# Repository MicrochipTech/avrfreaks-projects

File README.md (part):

# AVRFreaks Projects

The projects listed here are not owned nor managed by Microchip Technology Incorporated. See [Website Terms and Conditions](https://www.microchip.com/en-us/about/legal-information/website-terms-and-conditions) for terms and conditions.

## Projects

- [FatFS SD Card atmega328p](projects/fatfs-sd-card-atmega328p)
- [simple CAN TRANSMITTER & CAN RECEIVER with ATTINY804 , MCP2515 in ASSEMBLY](projects/simple-can-transmitter-can-receiver-attiny804-mcp2515-assembly)
- [USB HID Volume Control using ATmega16 with Rotary Encoder input](projects/usb-hid-volume-control-using-atmega16-rotary-encoder-input)
- [MAX7219 LED MATRIX clock with DS3231 and ATTINY 804 in ASSEMBLY](projects/max7219-led-matrix-clock-ds3231-and-attiny-804-assembly)
- [prnf](projects/prnf)
- [How-to select an optimal AVR type](projects/how-select-optimal-avr-type)
- [FP_display_for_UNO_V2](projects/fpdisplayforunov2)
- [DS1307 clock with menu , Attiny804, Assembly](projects/ds1307-clock-menu-attiny804-assembly)
- [HX711 raw data reader,Attiny804,assembly](projects/hx711-raw-data-readerattiny804assembly)
- [HX-711 , Attiny804 weighing scale ,ASM , assembly](projects/hx-711-attiny804-weighing-scale-asm-assembly)
- [Mouse Mover](projects/mouse-mover)
- [Floating_point_numbers: An investigation](projects/floatingpointnumbers-investigation)
- [Interfacing SSD1306 based 128x64 I2C OLED module without Frame Buffer and 4 input keys with 8-pin ATtiny85 in Assembly Code](projects/interfacing-ssd1306-based-128x64-i2c-oled-module-without-frame-buffer-and-4-input-keys-8)
- [Floating point display for the UNO](projects/floating-point-display-uno)
- [temperature controlled dc fan using atmega8](projects/temperature-controlled-dc-fan-using-atmega8)
- [APL - VGA, Audio and PS2 keyboard library](projects/apl-vga-audio-and-ps2-keyboard-library)
- [WB2812_Tiny25](projects/wb2812tiny25)
- [UNO_as_UPDI_programmer](projects/unoasupdiprogrammer)
- [Attiny804 basic USART transmit in assembly](projects/attiny804-basic-usart-transmit-assembly)
- [8086 emulator on Arduino UNO (atmega328p)](projects/8086-emulator-arduino-uno-atmega328p)
- [Attiny10 OLED Simple I2C Bitbang master in assembly with fonts](projects/attiny10-oled-simple-i2c-bitbang-master-assembly-fonts)
- [Attiny13 200psi pressure gauge 1602 Hitachi LCD with I2C backpack bitbang](projects/attiny13-200psi-pressure-gauge-1602-hitachi-lcd-i2c-backpack-bitbang)
- [ATTINY 804 Simple hardware I2C for Hitachi1602 LCD](projects/attiny-804-simple-hardware-i2c-hitachi1602-lcd)
- [Keypad & LCD in AVR Assembler](projects/keypad-lcd-avr-assembler)
- [AVRjs](projects/avrjs)
- [LM35](projects/lm35)
- [SAMV71 XPlained Ultra -- QSPI MEMORY MODE -- DMA](projects/samv71-xplained-ultra-qspi-memory-mode-dma)
- [Labels Counter Rev2](projects/labels-counter-rev2)
- [AVRUtils - I/O Abstraction](projects/avrutils-io-abstraction)
- [A8Eprog 1.00](projects/a8eprog-100)
- [SD Card MIDI Player](projects/sd-card-midi-player)
- [Arduino RTC Alarm Clock](projects/arduino-rtc-alarm-clock)
- [Stepper motor drive for telescope](projects/stepper-motor-drive-telescope)
- [MEGA TETRIS board (ATmega RGB LED display with pack of classic games and UART control)](projects/mega-tetris-board-atmega-rgb-led-display-pack-classic-games-and-uart-control)
- [Universal I/O C++ classes that should work with all 8bit AVRs](projects/universal-io-c-classes-should-work-all-8bit-avrs)
- [Capacitance meter with a current source to measure C from 1 pF to 400+ mF range](projects/capacitance-meter-current-source-measure-c-1-pf-400-mf-range)
- [A 540 Lumen Bike Light](projects/540-lumen-bike-light)
- [Single Letter Reader](projects/single-letter-reader)
- [Another Led Game](projects/another-led-game)
- [Full duplex software serial port](projects/full-duplex-software-serial-port)
- [I2C EEPROM Library](projects/i2c-eeprom-library)
- [TCPSimDBG VB Example v1](projects/tcpsimdbg-vb-example-v1)
- [Butterfly_RTC_demo](projects/butterflyrtcdemo)
- [Two AVR USART Communication](projects/two-avr-usart-communication)
- [AVR Sim Debug , TCPSimDBG](projects/avr-sim-debug-tcpsimdbg)
- [YABC (yet another boring clock)](projects/yabc-yet-another-boring-clock)
- [Temperature alarm](projects/temperature-alarm)
- [ROBOCON 2009](projects/robocon-2009)
- [4x25W amplifier with usb control](projects/4x25w-amplifier-usb-control)
- [Simple Led Cross](projects/simple-led-cross)
- [hexapode](projects/hexapode)
- [tmep_collector](projects/tmepcollector)
- [8/16/32/64b Math routines v2.0](projects/8163264b-math-routines-v20)
- [Bin2Dec](projects/bin2dec)
- [LCF Meter v1.2](projects/lcf-meter-v12)
- [Hex to Ascii Blitzschnell](projects/hex-ascii-blitzschnell)
- [ATMEGA32 BOARD](projects/atmega32-board)
- [COMMUNICATION BETWEEN 2 MCU](projects/communication-between-2-mcu)
- [Mega644 video generation](projects/mega644-video-generation)
- [AVR sound Recorder with MMC](projects/avr-sound-recorder-mmc)
- [RPM & Temperature & Gass Monitor](projects/rpm-temperature-gass-monitor)
- [New explorer for Atmega](projects/new-explorer-atmega)
- [I2C external EEProm Library](projects/i2c-external-eeprom-library)
- [Driver display 320x240](projects/driver-display-320x240)
- [Connect SD/MMC to atmega](projects/connect-sdmmc-atmega)
- [A simple RPM ATmega8](projects/simple-rpm-atmega8)
- [Bluetooth Based Smart Home](projects/bluetooth-based-smart-home)
- [taskswitch](projects/taskswitch)
- [IR Remote Controlled Car](projects/ir-remote-controlled-car)
- [Temperature Data Logger](projects/temperature-data-logger)
- [Temperature meter](projects/temperature-meter)
- [attiny26 ADC convertion](projects/attiny26-adc-convertion)
- [attiny26 dual PWM output](projects/attiny26-dual-pwm-output)
- [NGW100 Led Blink C program AVR32](projects/ngw100-led-blink-c-program-avr32)
- [My development boards for ATmega](projects/my-development-boards-atmega)
- [Efficient key debounce](projects/efficient-key-debounce)
- [Fast/Easy Switch Debouncer](projects/fasteasy-switch-debouncer)
- [Fast raw AVR ethernet for I/O](projects/fast-raw-avr-ethernet-io)
- [Control DDS-60 RF Synthesizer](projects/control-dds-60-rf-synthesizer)
- [Sony IR Remote Decoder](projects/sony-ir-remote-decoder)
- [Morse Code Practice Unit](projects/morse-code-practice-unit)
- [TeslaPhonic Organ V2, (update)V3](projects/teslaphonic-organ-v2-updatev3)
- [simple 7-seg counter](projects/simple-7-seg-counter)
- [AVR BootLoader 4 Mega32](projects/avr-bootloader-4-mega32)
- [Digital comb filter (humnuller)](projects/digital-comb-filter-humnuller)
- [Temperature via AVR-USB](projects/temperature-avr-usb)
- [TLC4541 dirver - 16 bit AD by TI](projects/tlc4541-dirver-16-bit-ad-ti)
- [Timer0 Interrupt handling](projects/timer0-interrupt-handling)
- [ATMEGA8 Development Board](projects/atmega8-development-board)
- [Flexible 4 bit LCD mode](projects/flexible-4-bit-lcd-mode)
- [WINDOWS STUDIO+ IDE Source Code](projects/windows-studio-ide-source-code)
- [Remote Controlled Car](projects/remote-controlled-car)
- [M-sequence (MLS) Generator](projects/m-sequence-mls-generator)
- [Graphical LCD Oscilloscope V2.0](projects/graphical-lcd-oscilloscope-v20)
- [I2C EEPROM Reader/Writer](projects/i2c-eeprom-readerwriter)
- [Washing machine](projects/washing-machine)
- [Automatic pet feeder](projects/automatic-pet-feeder)
- [RC5 Receiver for 16 leds](projects/rc5-receiver-16-leds)
- [Digital capacimeter](projects/digital-capacimeter)
- [HF generator](projects/hf-generator)
- [Motorized astronomy telescope](projects/motorized-astronomy-telescope)
- [AP7 PS2 Keyboard Driver](projects/ap7-ps2-keyboard-driver)
- [Versatile digital speedometer](projects/versatile-digital-speedometer)
- [DS1821 Thermometer](projects/ds1821-thermometer)
- [Harddisk Interface](projects/harddisk-interface)
- [Reaction game with AVR 90s2313](projects/reaction-game-avr-90s2313)
- [4x4 Matrix Key-board Interfacing](projects/4x4-matrix-key-board-interfacing)
- [AP7 mouse driver](projects/ap7-mouse-driver)
- [Atmega2560 BootLoader](projects/atmega2560-bootloader)
- [Basic LED Prjct Using Interrupt](projects/basic-led-prjct-using-interrupt)
- [DIY ATmega32 Starter's Kit](projects/diy-atmega32-starters-kit)
- [CAN Bus Driver for AT90CAN128 including FreeRTOS interface](projects/can-bus-driver-at90can128-including-freertos-interface)
- [True Random Number Generator](projects/true-random-number-generator)
- [PWM DC motor control with mega8](projects/pwm-dc-motor-control-mega8)
- [8-Channel ADC with Atmega32](projects/8-channel-adc-atmega32)
- [NOKIA3310 LCD Thermometer](projects/nokia3310-lcd-thermometer)
- [AVCX: AVR based LCD controller](projects/avcx-avr-based-lcd-controller)
- [AVR Scope Clock shield V3.A](projects/avr-scope-clock-shield-v3a)
- [gps demo for EVK1100](projects/gps-demo-evk1100)
- [WiSHABI](projects/wishabi)
- [TI-99/4A PS/2 Keyboard Interface](projects/ti-994a-ps2-keyboard-interface)
- [AVR - Lego Car](projects/avr-lego-car)
- [Interfacing External Interrupts](projects/interfacing-external-interrupts)
- [EA DOG-M 16X SPI C++ Library](projects/ea-dog-m-16x-spi-c-library)
- [Analog measurements and logger](projects/analog-measurements-and-logger)
- [AVGA v0.2](projects/avga-v02)
- [PT-100 Temperature sensor](projects/pt-100-temperature-sensor)
- [Accelerometer Reader](projects/accelerometer-reader)
- [termostat](projects/termostat)
- [Brake light blink](projects/brake-light-blink)
- [Driver for Nand flash memory](projects/driver-nand-flash-memory)
- [Driver for display Nokia 6100](projects/driver-display-nokia-6100)
- [Homebrew Case for the STK-500](projects/homebrew-case-stk-500)
- [MultiKit Digital Oscilloscope](projects/multikit-digital-oscilloscope)
- [Lndkavr](projects/lndkavr)
- [DigitalFrame MiniCommander](projects/digitalframe-minicommander)
- [USB Dance Pad](projects/usb-dance-pad)
- [basic tune player](projects/basic-tune-player)
- [PWM mit ATMEGA8](projects/pwm-mit-atmega8)
- [Investment Banker Eliminator](projects/investment-banker-eliminator)
- [Function Gen on Scope Clock](projects/function-gen-scope-clock-0)
- [AVR/FPGA digital synthesizer](projects/avrfpga-digital-synthesizer)
- [AtMega8535 PF Correction Relay](projects/atmega8535-pf-correction-relay)
- [4-digit lock code](projects/4-digit-lock-code)
- [MIDI controller](projects/midi-controller)
- [PPPD PCB (STK200/300 programmer)](projects/pppd-pcb-stk200300-programmer)
- [zero cost Logic Analyzer](projects/zero-cost-logic-analyzer)
- [temprature control using at90853](projects/temprature-control-using-at90853)
- [LM34DZ Temp Sensor on AVR](projects/lm34dz-temp-sensor-avr)
- [Dallas one-wire interface](projects/dallas-one-wire-interface)
- [Driver for Hd44780 8bit data bus](projects/driver-hd44780-8bit-data-bus)
- [16x2 LCD Libraries.](projects/16x2-lcd-libraries)
- [ATmega8 Devlopment  Board](projects/atmega8-devlopment-board)
- [Interfacing 4 buttons to the AVR](projects/interfacing-4-buttons-avr)
- [First C Project](projects/first-c-project)
- [Metronome](projects/metronome-0)
- [AVR-mUPI: A Unified Programming Interface for ATMEL® megaAVR devices.](projects/avr-mupi-unified-programming-interface-atmel%C2%AE-megaavr-devices)
- [Modbus RTU Slave Library for the avr](projects/modbus-rtu-slave-library-avr)
- [TOSHIBA T6963C DISPLAY DRIVE MADE IN C++ FOR AVR](projects/toshiba-t6963c-display-drive-made-c-avr)
- [Eclipse plugin for UART communication using USBasp+ programmer](projects/eclipse-plugin-uart-communication-using-usbasp-programmer)
- [Soft timers](projects/soft-timers-0)
- [3 servo claw arm](projects/3-servo-claw-arm)
- [PhoenixU1 (porting the Unix v1 to Atmega 8-bit)](projects/phoenixu1-porting-unix-v1-atmega-8-bit)
- [simple programablle count down timer](projects/simple-programablle-count-down-timer)
- [HD44780 Display Drive V2.00 C++](projects/hd44780-display-drive-v200-c)
- [Loader and recorder for ZX Spectrum on SD/SDHC](projects/loader-and-recorder-zx-spectrum-sdsdhc)
- [PWM mixed  Drive using ATMega8](projects/pwm-mixed-drive-using-atmega8)
- [HWA : high-level, no penalty hardware abstraction for microcontrollers](projects/hwa-high-level-no-penalty-hardware-abstraction-microcontrollers)
- [AVR32 UC3 Assembly example](projects/avr32-uc3-assembly-example)
- [A PC to uC IR Messaging system](projects/pc-uc-ir-messaging-system)
- [Bangla Voice Calling Bell](projects/bangla-voice-calling-bell)
- [AVR SPI IO Expander](projects/avr-spi-io-expander)
- [Basic AVR IO for LED Bar](projects/basic-avr-io-led-bar)
- [AVR231 AES Boot Loader](projects/avr231-aes-boot-loader)
- [AVR313 - PS2 Keyboard](projects/avr313-ps2-keyboard)
- [16.16 signed binary math lib.](projects/1616-signed-binary-math-lib)
- [ATMEGA16 to NOKIA8310LCD](projects/atmega16-nokia8310lcd)
- [Household power logger](projects/household-power-logger)
- [ADC using capacitor](projects/adc-using-capacitor)
- [Up/Down Timer Clock](projects/updown-timer-clock)
- [OSCCAL Calibration Program](projects/osccal-calibration-program)
- [Robotic Rescue Vehicle](projects/robotic-rescue-vehicle)
- [Simple ADC interface with LDR](projects/simple-adc-interface-ldr)
- [Sharp's GP2D02 Digital IR sensor](projects/sharps-gp2d02-digital-ir-sensor)
- [AVR Color LCD 320x240](projects/avr-color-lcd-320x240)
- [STK500 Binary Counter Demo](projects/stk500-binary-counter-demo)
- [Simple Projects](projects/simple-projects)
- [Temperature by SMT160 & AVR](projects/temperature-smt160-avr)
- [AVR BASED _ pre-amplifier + AGC](projects/avr-based-pre-amplifier-agc)
- [MyUSB Vendor defined demo](projects/myusb-vendor-defined-demo)
- [Multitherm](projects/multitherm)
- [ATtiny24/44/84 STK500 Adapter](projects/attiny244484-stk500-adapter)
- [GAS Detector](projects/gas-detector)
- [LCD2USB Button Fixed for Windows](projects/lcd2usb-button-fixed-windows)
- [ADC Using ATmega32](projects/adc-using-atmega32)
- [hd61830 library](projects/hd61830-library)
- [AVR SuperMario](projects/avr-supermario)
- [Microcontroller Oscilloscope](projects/microcontroller-oscilloscope)
- [rgb leds controlled by I2C](projects/rgb-leds-controlled-i2c)
- [5x7 led matrix demo (beginners)](projects/5x7-led-matrix-demo-beginners)
- [Lcd Clock](projects/lcd-clock)
- [IR (InfraRed) AVR Downloader](projects/ir-infrared-avr-downloader)
- [Pulse shifter (lag and lead)](projects/pulse-shifter-lag-and-lead)
- [RC1 transmitter using AVR 8535](projects/rc1-transmitter-using-avr-8535)
- [UART with FIFO](projects/uart-fifo)
- [3 axis bipolar stepper motor..](projects/3-axis-bipolar-stepper-motor)
- [Control de Motor Paso a Paso](projects/control-de-motor-paso-paso)
- [I2C (TWI) Sniffer](projects/i2c-twi-sniffer)
- [ultrasonics water height level](projects/ultrasonics-water-height-level)
- [Chameleon](projects/chameleon)
- [avr 20 servo controller](projects/avr-20-servo-controller)
- [Wiz810MJ with Bascom-AVR](projects/wiz810mj-bascom-avr)
- [Delay LOOPs](projects/delay-loops)
- [Project Buggy](projects/project-buggy)
- [22-bit voltmeter using AD7714](projects/22-bit-voltmeter-using-ad7714)
- [Anchor Winch Controller](projects/anchor-winch-controller)
- [Learn Code Vision](projects/learn-code-vision)
- [ethernet enc28j60 mega32](projects/ethernet-enc28j60-mega32)
- [Telephone Keypad](projects/telephone-keypad)
- [SD card reader for ATMega48](projects/sd-card-reader-atmega48)
- [RC Signal Reader](projects/rc-signal-reader)
- [External EEPROMs](projects/external-eeproms)
- [V/F & SVP demo on ATAVRMC200](projects/vf-svp-demo-atavrmc200)
- [Push Button Interfacing(Newbies)](projects/push-button-interfacingnewbies)
- [Arduino POV](projects/arduino-pov)
- [Decorative LEDs (For newbies)](projects/decorative-leds-newbies)
- [pC/OS - RTOS (realtime-kernel)](projects/pcos-rtos-realtime-kernel)
- [SIRC Decoding - Sony 12-bit IR](projects/sirc-decoding-sony-12-bit-ir)
- [Serial Connection With Labview](projects/serial-connection-labview)
- [Serial_LCD](projects/seriallcd)
- [BC100](projects/bc100)
- [UART C++ library](projects/uart-c-library)
- [VGA Display for STK500/501](projects/vga-display-stk500501)
- [LED Matrix](projects/led-matrix)
- [AVR uisp adapter for breadboard](projects/avr-uisp-adapter-breadboard)
- [MCUMenuObj 0.2](projects/mcumenuobj-02)
- [LCD-Driver](projects/lcd-driver)
- [JDTC](projects/jdtc)
- [HD44780's STDIO bind](projects/hd44780s-stdio-bind)
- [PCD 8544 LCD Driver](projects/pcd-8544-lcd-driver)
- [Thermometer with SMT160 on 7-seg](projects/thermometer-smt160-7-seg)
- [SW-UART up to 460800 Baud](projects/sw-uart-460800-baud)
- [Ultrasonic Resonant Tracking](projects/ultrasonic-resonant-tracking)
- [Accumulated PWM sinewave](projects/accumulated-pwm-sinewave)
- [Simple Traffic light controller](projects/simple-traffic-light-controller-0)
- [InfraRed Receiver](projects/infrared-receiver)
- [ads7816p driver](projects/ads7816p-driver)
- [Program HCS412 and HCS515 memory](projects/program-hcs412-and-hcs515-memory)
- [ADC voltage on 7seg at ATMEGA8](projects/adc-voltage-7seg-atmega8)
- [Rijndael / AES](projects/rijndael-aes)
- [Run AVR's from < 1 Volt](projects/run-avrs-1-volt)
- [Atmega training board](projects/atmega-training-board)
- [2.4 GHz Wireless Development Kit](projects/24-ghz-wireless-development-kit)
- [Wireless accelerometer mouse](projects/wireless-accelerometer-mouse)
- [Sound measuring decibel meter](projects/sound-measuring-decibel-meter)
- [my_ds18b20](projects/myds18b20)
- [ATtiny12 Stepper Motor Driver](projects/attiny12-stepper-motor-driver)
- [New Idea](projects/new-idea)
- [LotusLaser](projects/lotuslaser)
- [AVR 2.4 GHz  wireless RF module](projects/avr-24-ghz-wireless-rf-module)
- [XRay Dosimeter](projects/xray-dosimeter)
- [2D and 3D video on mega32](projects/2d-and-3d-video-mega32)
- [Conway's AI-Life for an AVR](projects/conways-ai-life-avr)
- [Dehumidifier Pump](projects/dehumidifier-pump)
- [WinLCDBitMap Version 1.0](projects/winlcdbitmap-version-10)
- [Pressure and stroke sensor](projects/pressure-and-stroke-sensor)
- [Isolated DC/DC Converter](projects/isolated-dcdc-converter)
- [Disassembler ATMEL AVR](projects/disassembler-atmel-avr)
- [Open GPS Tracker](projects/open-gps-tracker)
- [project](projects/project)
- [Network Biometric Authentication](projects/network-biometric-authentication)
- [AVR32 UC3 Serial Data Analyzer](projects/avr32-uc3-serial-data-analyzer)
- [Throttle System](projects/throttle-system)
- [LCD HD44780 C++ library](projects/lcd-hd44780-c-library)
- [Exposure timer](projects/exposure-timer)
- [Vacuum Tube Tester](projects/vacuum-tube-tester)
- [A (very) general controller](projects/very-general-controller)
- [Big Capacitor Stepper](projects/big-capacitor-stepper)
- [Programmable Relay](projects/programmable-relay)
- [Student Mega32 projects 2008](projects/student-mega32-projects-2008)
- [4x4x1](projects/4x4x1)
- [AVRsulabh- Parallel Programmer](projects/avrsulabh-parallel-programmer)
- [Nikon IR release](projects/nikon-ir-release)
- [Interrupt-based USART output](projects/interrupt-based-usart-output)
- [interrupt controlled button](projects/interrupt-controlled-button)
- [WebCam servo control](projects/webcam-servo-control)
- [Onewire lock system](projects/onewire-lock-system)
- [UAV parafoil](projects/uav-parafoil)
- [UTFT Fork which supports Fonts created by The Dot Factory](projects/utft-fork-which-supports-fonts-created-dot-factory)
- [hello_arduino](projects/helloarduino)
- [Motion Detector,Video Generator,Video GenLock with atmega64,atmega128](projects/motion-detectorvideo-generatorvideo-genlock-atmega64atmega128)
- [AVR Assembler Library for all microcontrollers with SRAM](projects/avr-assembler-library-all-microcontrollers-sram)
- [FeedTimer with ATMega328P](projects/feedtimer-atmega328p)
- [WS2812 LED Drive for ATmega8, ATMEGA162, ATmega128, ATmega328P](projects/ws2812-led-drive-atmega8-atmega162-atmega128-atmega328p)
- [Fix garage door with ATmega328p](projects/fix-garage-door-atmega328p)
- [Scientific Calculator](projects/scientific-calculator)
- [cojson - a JSON parser/generator for constrained platforms](projects/cojson-json-parsergenerator-constrained-platforms)
- [Tardyon Drive AVR Stepper Controller](projects/tardyon-drive-avr-stepper-controller)
- [FT232RL with optocouplers](projects/ft232rl-optocouplers)
- [A hotplug-capable DS1621/DS1631 temperature sensor library for the AVR](projects/hotplug-capable-ds1621ds1631-temperature-sensor-library-avr)
- [MAMoRo - Robot Platform](projects/mamoro-robot-platform)
- [sos Fuses manipulator for ATmega](projects/sos-fuses-manipulator-atmega)
- [FATEX-SD for EVK1100](projects/fatex-sd-evk1100)
- [AVRCryptoLib](projects/avrcryptolib)
- [M32 Clock Project](projects/m32-clock-project)
- [Control library for AD9833  DDS](projects/control-library-ad9833-dds)
- [Fuse Wizard](projects/fuse-wizard)
- [2 axis acceleration sensor](projects/2-axis-acceleration-sensor)
- [music recognizing dancing puppet](projects/music-recognizing-dancing-puppet)
- [Magic Laser aperture](projects/magic-laser-aperture)
- [uIP-0.9 With ENC18J60 Driver](projects/uip-09-enc18j60-driver)
- [MOS6581 SID Synthesizer](projects/mos6581-sid-synthesizer)
- [Power regulator/timer(ATMega8)](projects/power-regulatortimeratmega8)
- [Simple reaction tester with LCD](projects/simple-reaction-tester-lcd)
- [Countdown timer (ATtiny2313)](projects/countdown-timer-attiny2313)
- [uOLED-128-GMD1 interface](projects/uoled-128-gmd1-interface)
- [PID controller with anti-windup](projects/pid-controller-anti-windup)
- [Elmcie L- and C-meter](projects/elmcie-l-and-c-meter)
- [Moving average filter](projects/moving-average-filter)
- [ATtiny26 USI UART](projects/attiny26-usi-uart)
- [Servo driven robotic gripper](projects/servo-driven-robotic-gripper)
- [The Game of Life on an AVR](projects/game-life-avr)
- [LCD over one wire with ATtiny25](projects/lcd-over-one-wire-attiny25)
- [1-wire monitor](projects/1-wire-monitor)
- [Okapi](projects/okapi)
- [Resistor Network Calculator](projects/resistor-network-calculator)
- [Uni-polar stepper motor](projects/uni-polar-stepper-motor)
- [stepper motor driver](projects/stepper-motor-driver-1)
- [MMC Unlocker](projects/mmc-unlocker)
- [AVR DDS signal generator V2.0](projects/avr-dds-signal-generator-v20)
- [MidiController](projects/midicontroller)
- [Simple Traffic Light Controller](projects/simple-traffic-light-controller)
- [Cover paper for AVR Dragon kit](projects/cover-paper-avr-dragon-kit)
- [AVR Oscilloscope Clock](projects/avr-oscilloscope-clock)
- [AVR Flash Loader](projects/avr-flash-loader)
- [Terminalator II - The SQL](projects/terminalator-ii-sql)
- [AVR DB101 Demo gcc-Port](projects/avr-db101-demo-gcc-port)
- [trf24g RF module code](projects/trf24g-rf-module-code)
- [nRF2401 radio library](projects/nrf2401-radio-library)
- [library for 24cxx and 93cxx](projects/library-24cxx-and-93cxx)
- [Simple M168 Based Logic Analyzer](projects/simple-m168-based-logic-analyzer)
- [Fast LCD driver library](projects/fast-lcd-driver-library)
- [RF-talk](projects/rf-talk)
- [STK500 Example 2](projects/stk500-example-2)
- [9 floor elevator asm program](projects/9-floor-elevator-asm-program)
- [Speed Autobaud](projects/speed-autobaud)
- [CRC32 calculation functions](projects/crc32-calculation-functions)
- [Lib For Buffer](projects/lib-buffer)
- [AVR Oscilloscope Terminal](projects/avr-oscilloscope-terminal)
- [AVR446 ported for gcc](projects/avr446-ported-gcc)
- [Developer Terminal in C# and VB](projects/developer-terminal-c-and-vb)
- [YAVRTOS](projects/yavrtos)
- [Sparcle](projects/sparcle)
- [Intel Hex File Display Utility](projects/intel-hex-file-display-utility)
- [Refrash routine displays 240x320](projects/refrash-routine-displays-240x320)
- [YALBlinkie](projects/yalblinkie)
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
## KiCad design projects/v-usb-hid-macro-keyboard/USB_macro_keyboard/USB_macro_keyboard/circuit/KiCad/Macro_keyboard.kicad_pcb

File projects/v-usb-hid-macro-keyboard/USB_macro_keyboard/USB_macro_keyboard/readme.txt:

This is a package for project USB Macro_keyboard.

Main purpose of this project is to automate keboard presses with external tool that doesn't 
require install aditional software (so it works even on login screen of Windows OS or in BIOS).
It uses default HID keyboard drivers.

Sequence of keyboard signals is stored in eeprom. It can be uploaded via commandline tool or 
via standard SPI programming interface (although it might not be easy to get a proper addressing 
and also the attached schematic doesn't implement any programming connector on SPI interface).

Before programing make sure that your OS keyboard setting does match key mapping at the end of hid.c file.
To alter the code for your keyboard layout you can use table in Appendix C of Keyboard_scancodes_specification.pdf.
Additionals codes are in hid_keys.h that are also stored in eeprom memory but are used for device control
(e.g. timer delay - See function parseKeyBuffer in main.c file).

Original goal was to also create Windows program that can upload data to this device.
Unfortunately Windows handle keyboard drivers in a specific way and doesn't allow access to the device.
Because of that I decided to use signal on Num- and Caps-lock LEDs which are part of most of the keyboards.
After several presses of Num- and Caps-lock (or their combinations) it triggers corresponding procedure.

The commandline tool included is operating without too much problem on Linux system.
User has to have an access to USB ports or have root privilege. Also libusb-1.0 library is required.

Other limitation of this device is that it can only send key press and imidiate release. It can't
hold the key pressed for longer duration. Also it can send only one key at the time (not counting
modifiers keys like ctrl, alt and shift).

Special options can be selected in main_config.h (for example remove print function and some of the keys
to fit the code in attiny45) and usbconfig.h (change vendor/device name and VID/PID).

===Note for tiny85 clock source======================

Attiny85 can use its internal oscillator (with some calibration) to generate 16.5 MHz clock source.
I personaly can't recommend it since it was not reliable in my case. Sometimes the calibration
was not done correctly and the device didn't properly connect to USB driver. Therefore I decided
to use 12 MHz crystal instead.

At first I used whole calibration range but it never connected. USB specification probably require
faster device connection.
On second try I used only very small part of it but that required first to find out close to optimal
value of OSCCAL register. This was quite different between 2 chips I tested so the build phase
of the device was not simple.

Some of that old code is located in misc folder if you want to try it.

===Thanks goes to====================================

Objective development for V-USB library   https://www.obdev.at/products/vusb/index.html
Frank Zhao for explanation of HID descriptors   http://eleccelerator.com/tutorial-about-usb-hid-report-descriptors/
Joonas Pihlajamaa and his password generator example   http://codeandlife.com/2012/03/03/diy-usb-password-generator/

===Licensing========================================

Files in usbdrv folders are part of V-USB library from OBJECTIVE DEVELOPMENT Software GmbH - see License.txt
in that folder.

Other files are released under GNU GPLv3 license. See license.txt in root folder of this project.

===Content of the package===========================

circuit
	KiCad
		CustomPCD.pretty
			Diode_Zener.kicad_mod
			SOIC-8S2.kicad_mod
			USB_A_male.kicad_mod
		fp-lib-table
		Macro_keyboard-cache.lib
		Macro_keyboard.kicad_pcb
		Macro_keyboard.net
		Macro_keyboard.pro
		Macro_keyboard.sch
	PCB_bottom_mirrored.pdf
	Schematic.pdf
commandline
	macro_keyboard.cpp
	Makefile
firmware
	hid.c
	hid.h
	hid_keys.h
	hid_rq.h
	main.c
	main_config.h
	main.h
	Makefile
	timer.h
	usbconfig.h
	usbdrv
		asmcommon.inc
		CommercialLicense.txt
		Changelog.txt
		License.txt
		oddebug.c
		oddebug.h
		Readme.txt
		usbconfig-prototype.h
		usbdrvasm.asm
		usbdrvasm.lst
		usbdrvasm.o
		usbdrvasm.S
		usbdrvasm12.inc
		usbdrvasm128.inc
		usbdrvasm15.inc
		usbdrvasm16.inc
		usbdrvasm165.inc
		usbdrvasm18-crc.inc
		usbdrvasm20.inc
		usbdrv.c
		usbdrv.h
		USB-ID-FAQ.txt
		USB-IDs-for-free.txt
		usbportability.h
license.txt
misc
	bottom.jpg
	HID1_11.pdf
	Keyboard_scancodes_specification.pdf
	Old_code
		hid.c
		usbconfig.h
	side.jpg
	top.jpg
readme.txt

===================================================

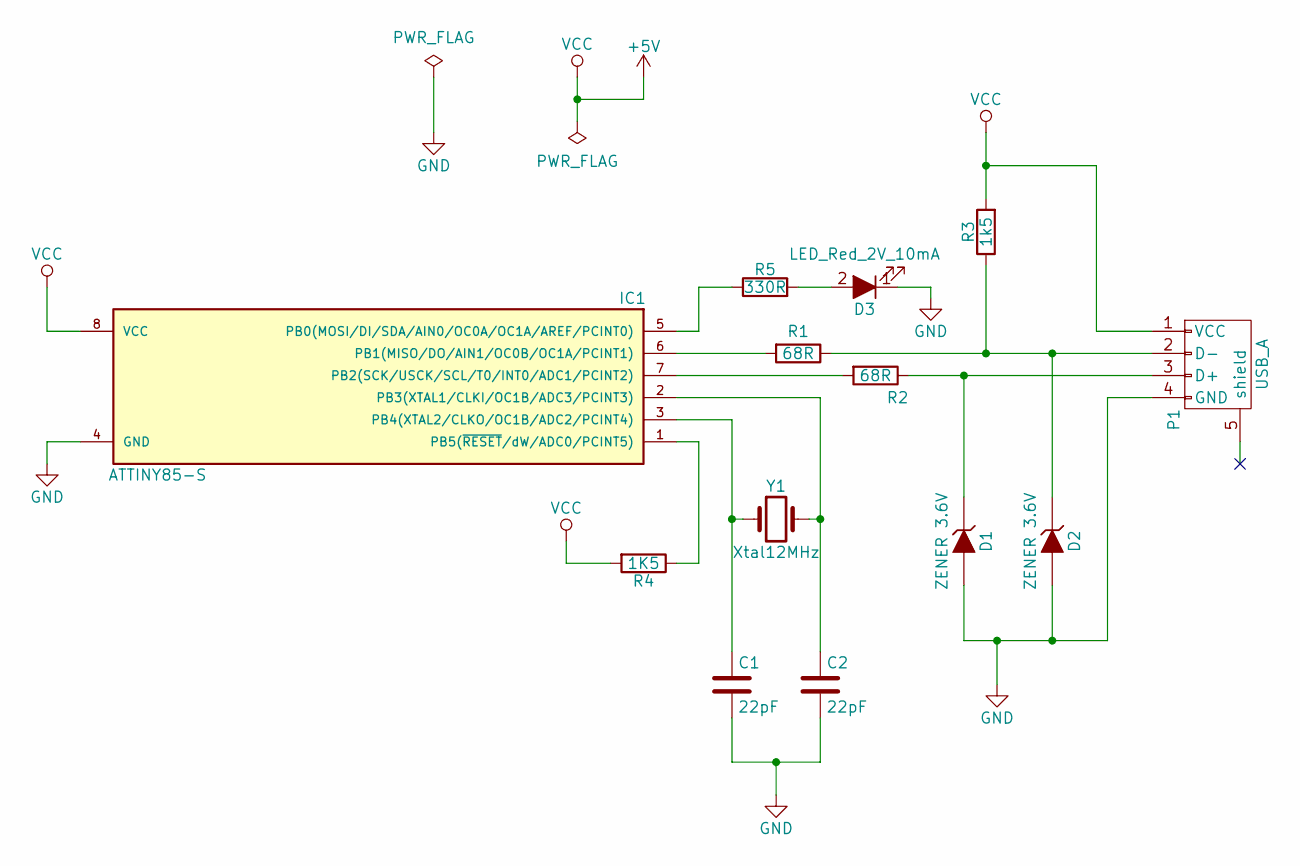
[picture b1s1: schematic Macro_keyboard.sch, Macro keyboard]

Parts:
C1, C2: 22pF; C_Disc_D4.3mm_W1.9mm_P5.00mm
D1, D2: ZENER 3.6V; Diode_Zener
D3: LED_Red_2V_10mA; LED_D3.0mm
IC1: ATTINY85-S; SOIC-8S2
P1: USB_A; USB_A_male
R1, R2: 68R; R_0805_HandSoldering
R3: 1k5; R_0805_HandSoldering
R4: 1K5; R_0805_HandSoldering
R5: 330R; R_Axial_DIN0207_L6.3mm_D2.5mm_P7.62mm_Horizontal
Y1: Xtal12MHz; Crystal_HC49-4H_Vertical

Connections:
+5V: IC1.8 (VCC), P1.1 (VCC), R3.2, R4.2
GND: C1.2, C2.2, D1.2 (A), D2.2 (A), D3.1 (K), IC1.4 (GND), P1.4 (GND)
unnamed: C1.1, IC1.3 (PB4(XTAL2/CLKO/OC1B/ADC2/PCINT4)), Y1.1
unnamed: C2.1, IC1.2 (PB3(XTAL1/CLKI/OC1B/ADC3/PCINT3)), Y1.2
unnamed: D1.1 (K), P1.3 (D+), R2.1
unnamed: D2.1 (K), P1.2 (D-), R1.1, R3.1
unnamed: D3.2 (A), R5.2
unnamed: IC1.1 (PB5(~RESET~/dW/ADC0/PCINT5)), R4.1
unnamed: IC1.5 (PB0(MOSI/DI/SDA/AIN0/OC0A/OC1A/AREF/PCI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), R5.1
unnamed: IC1.6 (PB1(MISO/DO/AIN1/OC0B/OC1A/PCINT1)), R1.2
unnamed: IC1.7 (PB2(SCK/USCK/SCL/T0/INT0/ADC1/PCINT2)), R2.2

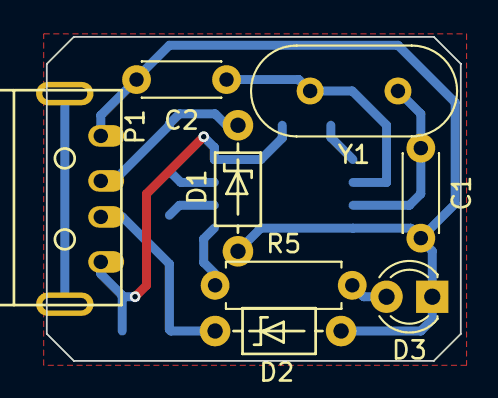
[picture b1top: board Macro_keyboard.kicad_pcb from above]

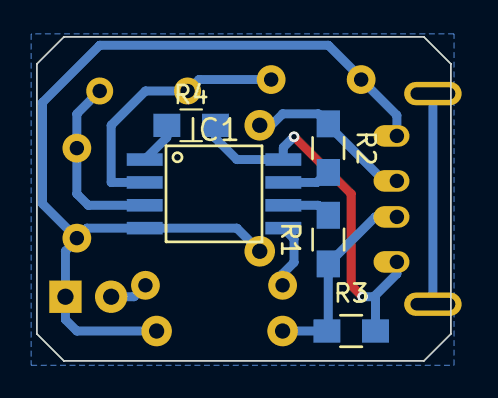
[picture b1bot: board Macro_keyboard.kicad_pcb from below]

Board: 2 copper layers, 23.0 x 18.0 mm, 13 parts (5 on the bottom side), 11 nets.

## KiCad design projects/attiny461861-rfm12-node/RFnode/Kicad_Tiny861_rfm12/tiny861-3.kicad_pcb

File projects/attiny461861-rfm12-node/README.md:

# ATtiny461/861 RFM12 node

Uploaded by stewarttodd on 2013-06-24 05:29:00 (rating 0 out of 5)

## Summary

Small PCB design using ATtiny 461/861 for RF linked remote temperature sensor with 1-wire sensor.  

Well suited for battery operation as most of the time is spent in sleep mode.  

Choose from multiple data-rates and RF channels.

I have several of these around (in and outside) my house. One sensor in my freezer (I always wondered what the temp was in there).  

The data is collated, stored on a SD card in an Arduino system and logged on the internet.

These are only used as transmitters, the receive side should also work fine but is untested.  

There are 4 other available I/O's on the PCB which can read analog or be used as digital I/O.

## Compilers

- AVR Assembler

## Tags

- Complete code with HW
- AVR Assembler

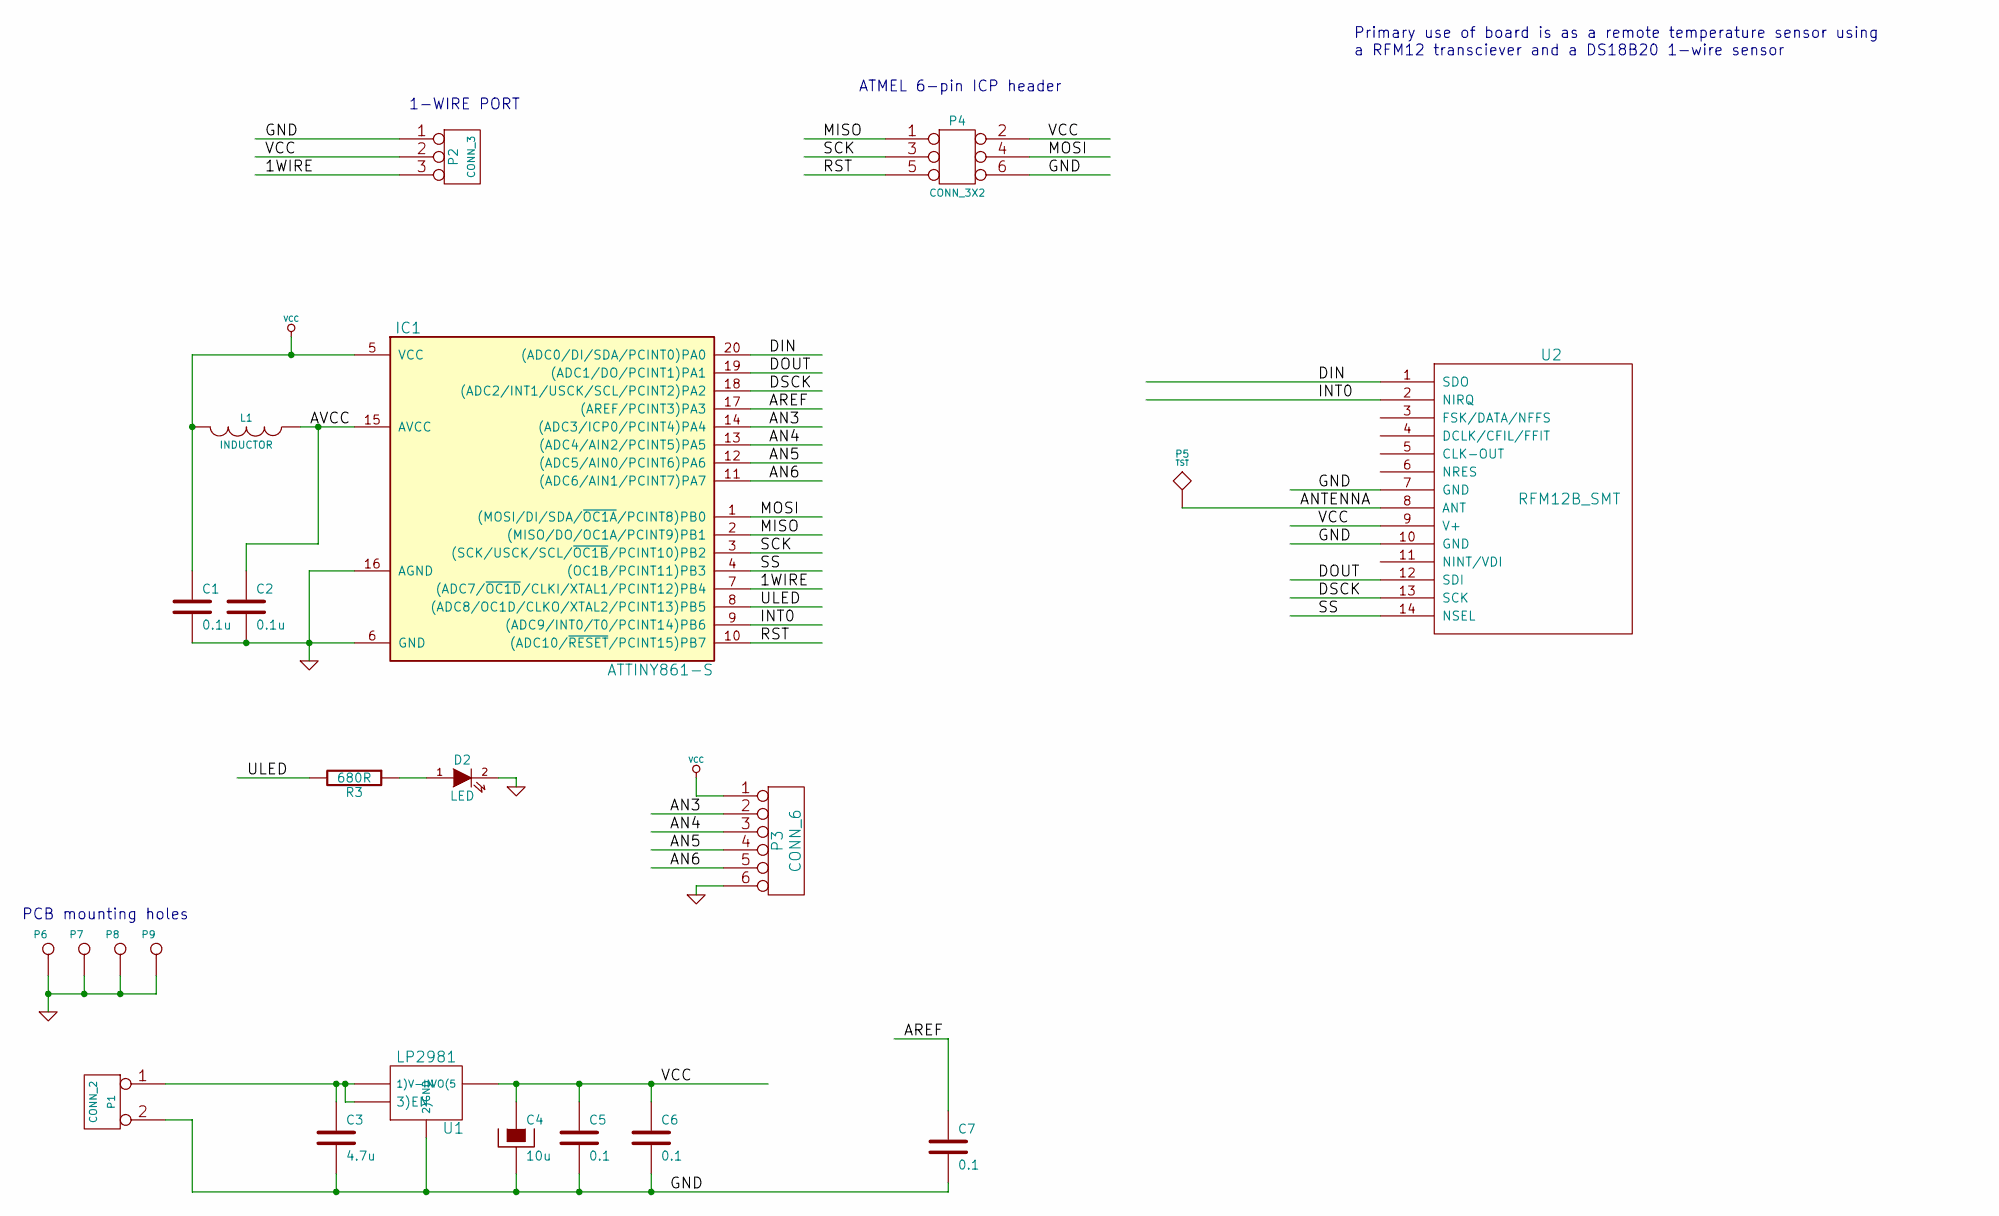
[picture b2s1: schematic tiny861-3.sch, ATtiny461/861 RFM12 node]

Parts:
C1, C2: 0.1u
C3: 4.7u
C4: 10u
C5, C6, C7: 0.1
D2: LED
IC1: ATTINY861-S; SO20
L1: INDUCTOR
P1: CONN_2
P2: CONN_3
P3: CONN_6
P4: CONN_3X2
P5: TST
P6, P7, P8, P9: CONN_1
R3: 680R
U1: LP2981
U2: RFM12B_SMT

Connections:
/1WIRE: IC1.7 ((ADC7/~OC1D~/CLKI/XTAL1/PCINT12)PB4), P2.3
/AN3: IC1.14 ((ADC3/ICP0/PCINT4)PA4), P3.2
/AN4: IC1.13 ((ADC4/AIN2/PCINT5)PA5), P3.3
/AN5: IC1.12 ((ADC5/AIN0/PCINT6)PA6), P3.4
/AN6: IC1.11 ((ADC6/AIN1/PCINT7)PA7), P3.5
/ANTENNA: P5.1, U2.8 (ANT)
/AREF: C7.1, IC1.17 ((AREF/PCINT3)PA3)
/AVCC: C2.1, IC1.15 (AVCC), L1.1
/DIN: IC1.20 ((ADC0/DI/SDA/PCINT0)PA0), U2.1 (SDO)
/DOUT: IC1.19 ((ADC1/DO/PCINT1)PA1), U2.12 (SDI)
/DSCK: IC1.18 ((ADC2/INT1/USCK/SCL/PCINT2)PA2), U2.13 (SCK)
/INT0: IC1.9 ((ADC9/INT0/T0/PCINT14)PB6), U2.2 (NIRQ)
/MISO: IC1.2 ((MISO/DO/OC1A/PCINT9)PB1), P4.1
/MOSI: IC1.1 ((MOSI/DI/SDA/~OC1A~/PCINT8)PB0), P4.4
/RST: IC1.10 ((ADC10/~RESET~/PCINT15)PB7), P4.5
/SCK: IC1.3 ((SCK/USCK/SCL/~OC1B~/PCINT10)PB2), P4.3
/SS: IC1.4 ((OC1B/PCINT11)PB3), U2.14 (NSEL)
/ULED: IC1.8 ((ADC8/OC1D/CLKO/XTAL2/PCINT13)PB5), R3.2
GND: C1.2, C2.2, C3.2, C4.2, C5.2, C6.2, C7.2, D2.2 (K), IC1.6 (GND), IC1.16 (AGND), P1.2 (PM), P2.1, P3.6, P4.6, P6.1, P7.1, P8.1, P9.1, U1.2 (2)GND), U2.7 (GND), U2.10 (GND)
unnamed: D2.1 (A), R3.1
unnamed: C3.1, P1.1, U1.1 (1)V-IN), U1.3 (3)EN)
VCC: C1.1, C4.1, C5.1, C6.1, IC1.5 (VCC), L1.2, P2.2 (PM), P3.1, P4.2, U1.5 (VO(5), U2.9 (V+)

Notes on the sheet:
PCB mounting holes
Primary use of board is as a remote temperature sensor using a RFM12 transciever and a DS18B20 1-wire sensor
1-WIRE PORT
ATMEL 6-pin ICP header

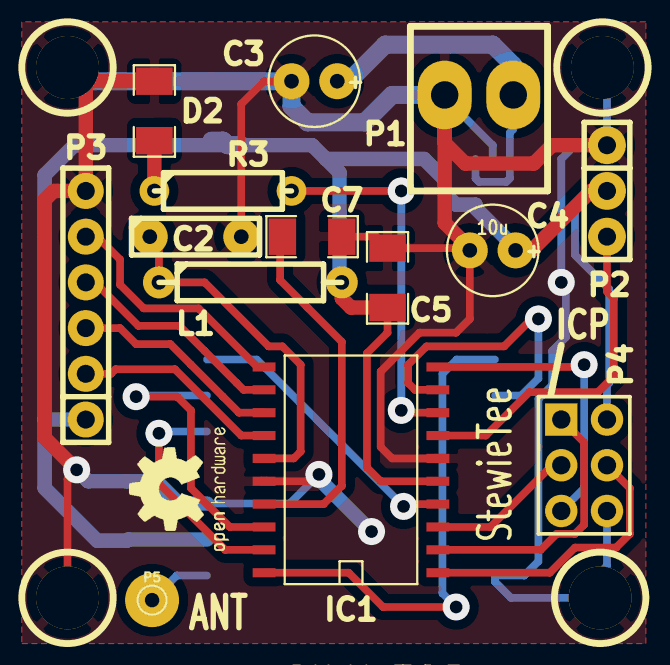
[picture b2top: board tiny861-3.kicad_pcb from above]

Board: 2 copper layers, 22 parts (0 on the bottom side), 22 nets.

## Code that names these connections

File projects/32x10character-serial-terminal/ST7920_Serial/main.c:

/*
 * main.c
 *
 *  Created on: Apr 8, 2013
 *      Author: Peter Barnes
 *
 *      Atmega 8 and ST7920-based 12864 display
 *      Serial data at 4800 baud (or whatever you choose below that) applied to pin 2, Rxd
 *      LED on PD2 will light up when receiving characters, will extinguish only when the 4-byte buffer is flushed by a carriage return or some other non-alphanumeric character.
 *
 *      12864 pins:
 *      1	Gnd
 *      2	Vcc
 *      3	Vo (contrast-to center of 10K pot between Vcc and Gnd)
 *      4	PC0
 *      5	PC1
 *      6	PC2
 *      7	PB0
 *      8	PB1
 *      9	PB2
 *      10	PB3
 *      11	PB4
 *      12	PB5
 *      13	PB6
 *      14	PB7
 *      15	Vcc	(PSB - parallel or serial. We're using the parallel interface.)
 *      16	Not Connected
 *      17	Atmega pin 1 (reset)
 *      18	Not Connected
 *      19	Vcc
 *      20	Gnd
 *
 */

#include "st7920.h"
#include <avr/interrupt.h>

// USART STUFF
#define UART_BAUDRATE 4800    //  4800 baud is the maximum possible with a 8MHz clock and this display
#define BAUD_PRESCALE (((F_CPU / (UART_BAUDRATE * 16UL))) - 1)
uint8_t usart_byte;
uint8_t byte_recvd_flag;

void USART_init();
char USARTReadChar(void);
uint8_t minibuffer[4];	// holder for received usart characters
//


int main(void)
{
	DDRD = 0xfe;    // set pin PD0 (USART RXD) for input
	USART_init();
	sei();

	int i, j, k;
    char string1[16] = "      USART     ";
    char string3[16] = "    4800 Baud   ";
    char string2[16] = "       8N1      ";
    char string4[16] = "  Barnes - 2013 ";
    DATAPORT_DIR = 0xff;    // set DATAPORT to output
    DATA_PORT = 0x00;    // set outputs to 0 initially
    COMMAND_DIR = 0x07;    // set command port to output
    COMMAND_PORT = 0x00;    // set outputs to 0 initially
    clcd_init();    // initialize as character display
    cdisplay_clear();    // clear character screen and reset address to 0
    // set_cgram_address(0, 0);
    for (i = 0; i < 16; ++i) {
        write_data(string1[i]);
    }
    for (i = 0; i < 16; ++i) {
        write_data(string2[i]);
    }
    for (i = 0; i < 16; ++i) {
        write_data(string3[i]);
    }
    for (i = 0; i < 16; ++i) {
        write_data(string4[i]);
    }
    _delay_ms(3000);
    cdisplay_clear();

    glcd_enable();
    glcd_fill(0x0000);

    draw_vertical_line(0,0,127);
    draw_vertical_line(0,63,127);

//	for (j = 0; j < 8; j++)
//    {
//			write_4chars_xy(j, 3, 32, 49, 50, 51);
//	}

    i=0;
    k=2;	// y column counter (will be multiplied by 6 to allow for the height of the characters, so value = 0 - 10.
	j=0;	// x row counter (0-7)
	while(1)
	{
		//Read data
	    usart_byte = USARTReadChar();
        {
            PORTD |= 4;		// turn on led on PD2
        	if ((usart_byte < 32) | (usart_byte > 127))	// NOTE: I've given up trying to implement a carriage return - takes too much time, we lose characters
			{
        		usart_byte = 31;	//
            }
       		minibuffer[i]= usart_byte;
       	    i++;
       	    if (i==4)
       	    {
       	    	PORTD &= 0xfb;	// turn led off (buffer is empty)
       	    	i=0;
       	    	write_4chars_xy(j, k, minibuffer[0], minibuffer[1], minibuffer[2], minibuffer[3]);
       	    	j++;
       	    	if (j==8)
       	    	{
       	    		j=0;
       	    		k += 6;		//  bump down to the next line
       	    		if (k > 59)	// if we've reached the bottom line
       	    		{
       	    			k = 2;
       	    		}
       	    	}
       	    }
       	    byte_recvd_flag = 0;        // and reset flag, wait for next character from USART
      	}
    }
}


void USART_init()
    {
		UCSRC=(1<<URSEL)|(3<<UCSZ0); // async., 8N1
		UCSRB=(1<<RXEN)|(1<<TXEN);
        UBRRL = BAUD_PRESCALE;
        UBRRH = (BAUD_PRESCALE >> 8);
    }

void USART_send_char(char b)
    {
        UDR = b;
        while(!(UCSRA&(1<<TXC)));
    }

char USARTReadChar()
{
   //	loop until data is available
   while(!(UCSRA & (1<<RXC))){}
   return UDR;
}

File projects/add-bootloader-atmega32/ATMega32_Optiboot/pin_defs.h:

#if defined(__AVR_ATmega168__) || defined(__AVR_ATmega328P__) || defined(__AVR_ATmega88) || defined(__AVR_ATmega8__) || defined(__AVR_ATmega88__)
/* Onboard LED is connected to pin PB5 in Arduino NG, Diecimila, and Duemilanove */ 
#define LED_DDR     DDRB
#define LED_PORT    PORTB
#define LED_PIN     PINB
#define LED         PINB5

/* Ports for soft UART */
#ifdef SOFT_UART
#define UART_PORT   PORTD
#define UART_PIN    PIND
#define UART_DDR    DDRD
#define UART_TX_BIT 1
#define UART_RX_BIT 0
#endif
#endif

#if defined(__AVR_ATmega8__) ||  defined(__AVR_ATmega32__)
  //Name conversion R.Wiersma
  #define UCSR0A	UCSRA
  #define UDR0 		UDR
  #define UDRE0 	UDRE
  #define RXC0		RXC
  #define FE0           FE
  #define TIFR1 	TIFR
  #define WDTCSR	WDTCR
#endif

/* Luminet support */
#if defined(__AVR_ATtiny84__)
/* Red LED is connected to pin PA4 */ 
#define LED_DDR     DDRA
#define LED_PORT    PORTA
#define LED_PIN     PINA
#define LED         PINA4
/* Ports for soft UART - left port only for now. TX/RX on PA2/PA3 */
#ifdef SOFT_UART
#define UART_PORT   PORTA
#define UART_PIN    PINA
#define UART_DDR    DDRA
#define UART_TX_BIT 2
#define UART_RX_BIT 3
#endif
#endif

/* Sanguino support */
#if defined(__AVR_ATmega644P__)
/* Onboard LED is connected to pin PB0 on Sanguino */ 
#define LED_DDR     DDRB
#define LED_PORT    PORTB
#define LED_PIN     PINB
#define LED         PINB0

/* Ports for soft UART */
#ifdef SOFT_UART
#define UART_PORT   PORTD
#define UART_PIN    PIND
#define UART_DDR    DDRD
#define UART_TX_BIT 1
#define UART_RX_BIT 0
#endif
#endif

/* Mega support */
#if defined(__AVR_ATmega1280__)
/* Onboard LED is connected to pin PB7 on Arduino Mega */ 
#define LED_DDR     DDRB
#define LED_PORT    PORTB
#define LED_PIN     PINB
#define LED         PINB7

/* Ports for soft UART */
#ifdef SOFT_UART
#define UART_PORT   PORTE
#define UART_PIN    PINE
#define UART_DDR    DDRE
#define UART_TX_BIT 1
#define UART_RX_BIT 0
#endif
#endif

/* EMK - ATMega32 support */
#if defined(__AVR_ATmega32__)
/* Onboard LED is connected to pin PB0 on ATMega32 */ 
#define LED_DDR     DDRB
#define LED_PORT    PORTB
#define LED_PIN     PINB
#define LED         PINB0

/* Ports for soft UART */
#ifdef SOFT_UART
#define UART_PORT   PORTD
#define UART_PIN    PIND
#define UART_DDR    DDRD
#define UART_TX_BIT 1
#define UART_RX_BIT 0
#endif
#endif

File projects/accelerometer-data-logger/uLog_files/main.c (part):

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#define BAUD 9600
#define MYUBRR FOSC/16/BAUD-1

#define SCK 3	//PA3
#define SI 1	//PB1
#define SO 7	//PA7
#define CS 2	//PB2

#define STAT 0	//PB0


//Define functions
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	
	DIDR0 = 0x07;//digital input disable ADC lines
	
	DDRA = 0b01001000;//PA6 = out (TX/MOSI), PA3 = SCK
	PORTB = 0x07;
	DDRB = 0b00000111;//PB0 = stat, PB1 = SI (local output), PB2 = CS // PB0 is sinking LED
	
	//setup timer0
	TCCR0B = 2;//clk/8
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
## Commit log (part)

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2022-03-17 Import from https://community.atmel.com/projects/xplain-pdiserial-bridge
2022-03-17 Import from https://community.atmel.com/projects/attiny85-sending-byte-74hc595
2022-03-17 Import from https://community.atmel.com/projects/distance-measurement-using-atmega328p-and-hc-sr04
2022-03-17 Import from https://community.atmel.com/projects/mynetpcb
2022-03-17 Import from https://community.atmel.com/projects/avr-hal-atmega-series
2022-03-17 Import from https://community.atmel.com/projects/avr-asm-simulator
2022-03-17 Import from https://community.atmel.com/projects/line-following-robot
2022-03-17 Import from https://community.atmel.com/projects/atxmega-starter-board-sdram
2022-03-17 Import from https://community.atmel.com/projects/mod-player-avr-8-bit-atmega
2022-03-17 Import from https://community.atmel.com/projects/hm55b-compass-module-reader
2022-03-17 Import from https://community.atmel.com/projects/hd44780-char-lcd-interface
2022-03-17 Import from https://community.atmel.com/projects/communication-aid-system
2022-03-17 Import from https://community.atmel.com/projects/lcd-midi-data-display
2022-03-17 Import from https://community.atmel.com/projects/usbasp-64bit-windows
2022-03-17 Import from https://community.atmel.com/projects/atmel-qtouch-guidesexamples
2022-03-17 Import from https://community.atmel.com/projects/rs-484-communication
2022-03-17 Import from https://community.atmel.com/projects/binary-ascii-formatter
2022-03-17 Import from https://community.atmel.com/projects/complete-bitmap-hex-converter
2022-03-17 Import from https://community.atmel.com/projects/avr-butterfly-mp3-player
2022-03-17 Import from https://community.atmel.com/projects/3in1-motor-stepper-controller
2022-03-17 Import from https://community.atmel.com/projects/scrolly-led-matrix-clock
2022-03-17 Import from https://community.atmel.com/projects/ad7705-16-bit-adc-atmega-644
2022-03-17 Import from https://community.atmel.com/projects/temperature-monitor-xbee
2022-03-17 Import from https://community.atmel.com/projects/pluto-board-28-pin-proto-board
2022-03-17 Import from https://community.atmel.com/projects/avr-butterfly-real-time-clock
2022-03-17 Import from https://community.atmel.com/projects/supermodified
2022-03-17 Import from https://community.atmel.com/projects/baud-rate-converter
2022-03-17 Import from https://community.atmel.com/projects/avrisp-c-compiled-flashing-leds
2022-03-17 Import from https://community.atmel.com/projects/e3-lcd-key-demo-code
2022-03-17 Import from https://community.atmel.com/projects/attiny26-melody-generator
2022-03-17 Import from https://community.atmel.com/projects/microcontrollers
2022-03-17 Import from https://community.atmel.com/projects/light-dimmer
2022-03-17 Import from https://community.atmel.com/projects/parallax-ping-sensor-n-atmega128
2022-03-17 Import from https://community.atmel.com/projects/panel8x8-library
2022-03-17 Import from https://community.atmel.com/projects/control-bipolar-stepper-motor
2022-03-17 Import from https://community.atmel.com/projects/simple-button-debouncing
2022-03-17 Import from https://community.atmel.com/projects/comparatorc-0
2022-03-17 Import from https://community.atmel.com/projects/traffic-lights-ecros-board
2022-03-17 Import from https://community.atmel.com/projects/blue-clock
2022-03-17 Import from https://community.atmel.com/projects/ultrasonic-and-infrared-scanner
2022-03-17 Import from https://community.atmel.com/projects/graphical-alarm-clock
2022-03-17 Import from https://community.atmel.com/projects/pymite
2022-03-17 Import from https://community.atmel.com/projects/comparatorc
2022-03-17 Import from https://community.atmel.com/projects/its-about-time
2022-03-17 Import from https://community.atmel.com/projects/jeenode
2022-03-17 Import from https://community.atmel.com/projects/stk-500-help-board
2022-03-17 Import from https://community.atmel.com/projects/osccal-calibration-using-32khz-x
2022-03-17 Import from https://community.atmel.com/projects/card-swipe-voting-system
2022-03-17 Import from https://community.atmel.com/projects/atmega8-test-board-module
2022-03-17 Import from https://community.atmel.com/projects/control-motor-using-l298-driver
2022-03-17 Import from https://community.atmel.com/projects/avr-assembly-syntax-highlighting-nano-under-linux
2022-03-17 Import from https://community.atmel.com/projects/nokia5110-graphical-display-interfacing-atmega16-32
2022-03-17 Import from https://community.atmel.com/projects/eeprom-wear-leveling-library
2022-03-17 Import from https://community.atmel.com/projects/tcd1304dg-driver-circuit-using-atmega1284p-mcu
2022-03-17 Import from https://community.atmel.com/projects/launch-controller-atmega8
2022-03-17 Import from https://community.atmel.com/projects/text-lcd-interface-avr
2022-03-17 Import from https://community.atmel.com/projects/afp-arbitrary-fixed-point-lib
2022-03-17 Import from https://community.atmel.com/projects/bcd-4digit-decoder-lcd
2022-03-17 Import from https://community.atmel.com/projects/stepper-motor-control
2022-03-17 Import from https://community.atmel.com/projects/rgb-pattern-generator
2022-03-17 Import from https://community.atmel.com/projects/programmer-and-bootloader
2022-03-17 Import from https://community.atmel.com/projects/lcd-dmf50840
2022-03-17 Import from https://community.atmel.com/projects/flickering-jack-o%C3%A2%E2%82%AC%E2%84%A2lantern-light
2022-03-17 Import from https://community.atmel.com/projects/household-water-heater-rf-ctrl
2022-03-17 Import from https://community.atmel.com/projects/attiny45-prototyping-board
2022-03-17 Import from https://community.atmel.com/projects/rgb-led-display-soft-pwm
2022-03-17 Import from https://community.atmel.com/projects/atmega48-rs232usb-devel-board
2022-03-17 Import from https://community.atmel.com/projects/power-supply-buck-converter
2022-03-17 Import from https://community.atmel.com/projects/atmega-ea-dogm128w-6
2022-03-17 Import from https://community.atmel.com/projects/line-follower-robot
2022-03-17 Import from https://community.atmel.com/projects/6-channel-rc-decoder
2022-03-17 Import from https://community.atmel.com/projects/flashing-light-watchdog-tim
2022-03-17 Import from https://community.atmel.com/projects/split-string
2022-03-17 Import from https://community.atmel.com/projects/glcd-lib-persian-glcd
2022-03-17 Import from https://community.atmel.com/projects/power-down-mode-example
2022-03-17 Import from https://community.atmel.com/projects/bamo32
2022-03-17 Import from https://community.atmel.com/projects/5-channel-a2d-converter
2022-03-17 Import from https://community.atmel.com/projects/avr-usuing-bbc-vdu-commands
2022-03-17 Import from https://community.atmel.com/projects/test-oscillator
2022-03-17 Import from https://community.atmel.com/projects/i%C3%A2%C2%B2c-twi-avr-butterfly
2022-03-17 Import from https://community.atmel.com/projects/flickering-christmas-candle
2022-03-17 Import from https://community.atmel.com/projects/usb-programmer-avr
2022-03-17 Import from https://community.atmel.com/projects/first-usart
2022-03-17 Import from https://community.atmel.com/projects/current-sense
2022-03-17 Import from https://community.atmel.com/projects/customizable-lcd-connection
2022-03-17 Import from https://community.atmel.com/projects/tellymate-serial-tv-adapter
2022-03-17 Import from https://community.atmel.com/projects/chess-timer
2022-03-17 Import from https://community.atmel.com/projects/hyperterminal-lcd-system-0
2022-03-17 Import from https://community.atmel.com/projects/usb-communication
2022-03-17 Import from https://community.atmel.com/projects/character-lcd-display-linux
2022-03-17 Import from https://community.atmel.com/projects/twii2c-arduino-atmega8
2022-03-17 Import from https://community.atmel.com/projects/hyperterminal-lcd-system
2022-03-17 Import from https://community.atmel.com/projects/naive-digital-synchronizer
2022-03-17 Import from https://community.atmel.com/projects/avr-vga-interface-module
2022-03-17 Import from https://community.atmel.com/projects/attiny2313-servo-controller
2022-03-17 Import from https://community.atmel.com/projects/big-dot-matrix-led-display-board
2022-03-17 Import from https://community.atmel.com/projects/low-cost-xmega
2022-03-17 Import from https://community.atmel.com/projects/atmega8-stepper-motor-controller
2022-03-17 Import from https://community.atmel.com/projects/avrselect
2022-03-17 Import from https://community.atmel.com/projects/avr-visual-programming
2022-03-17 Import from https://community.atmel.com/projects/task-scheduler-pattern-attiny104
2022-03-17 Import from https://community.atmel.com/projects/sam3x-arduino-due-hc-sr04-interrupts-reduce-asf-layers
2022-03-17 Import from https://community.atmel.com/projects/obstacle-avoider-robot
2022-03-17 Import from https://community.atmel.com/projects/powerful-tens-device
2022-03-17 Import from https://community.atmel.com/projects/three-simple-tens-circuits
2022-03-17 Import from https://community.atmel.com/projects/powerful-tes-circuit
2022-03-17 Import from https://community.atmel.com/projects/rc-polygot
2022-03-17 Import from https://community.atmel.com/projects/bluesky-projects-3
2022-03-17 Import from https://community.atmel.com/projects/phase-locked-loop
2022-03-17 Import from https://community.atmel.com/projects/my-testproject
2022-03-17 Import from https://community.atmel.com/projects/skeeball-brain
2022-03-17 Import from https://community.atmel.com/projects/atmega-menu-and-submenu-explorer
2022-03-17 Import from https://community.atmel.com/projects/picaxe
2022-03-17 Import from https://community.atmel.com/projects/mame-joystick-adapter
2022-03-17 Import from https://community.atmel.com/projects/gps-finder
2022-03-17 Import from https://community.atmel.com/projects/avrj1850vpwinterface
2022-03-17 Import from https://community.atmel.com/projects/tiny-10x10-led-matrix-board
2022-03-17 Import from https://community.atmel.com/projects/serial-relay-control
2022-03-17 Import from https://community.atmel.com/projects/atmega16-demoboard
2022-03-17 Import from https://community.atmel.com/projects/attiny2313-hd44780-interface
2022-03-17 Import from https://community.atmel.com/projects/usbloader
2022-03-17 Import from https://community.atmel.com/projects/siemens-s65-display-osziloscope
2022-03-17 Import from https://community.atmel.com/projects/opendous-jtag
2022-03-17 Import from https://community.atmel.com/projects/nice-gui-usbasp-programmer
2022-03-17 Import from https://community.atmel.com/projects/nokia-6100-lcd-driver
2022-03-17 Import from https://community.atmel.com/projects/%C3%A2%E2%82%AC%C5%93c-library%C3%A2%E2%82%AC%C2%9D-ks0108-graphical
2022-03-17 Import from https://community.atmel.com/projects/ps2-library
2022-03-17 Import from https://community.atmel.com/projects/ps2-keyboard-library
2022-03-17 Import from https://community.atmel.com/projects/quick-and-dirty-1wire-clk-rc1mhz
2022-03-17 Import from https://community.atmel.com/projects/gamecube-controller-interface
2022-03-17 Import from https://community.atmel.com/projects/simpel-code-use-adc
2022-03-17 Import from https://community.atmel.com/projects/robotkit-india
2022-03-17 Import from https://community.atmel.com/projects/irtos
2022-03-17 Import from https://community.atmel.com/projects/thermometer-lm35atmega48
2022-03-17 Import from https://community.atmel.com/projects/opendsc
2022-03-17 Import from https://community.atmel.com/projects/yamaha-tx81z-midi-programmer
2022-03-17 Import from https://community.atmel.com/projects/best-lcfrq-meter-nokia-lcd
2022-03-17 Import from https://community.atmel.com/projects/avr-sound-recorder-mmc-0
2022-03-17 Import from https://community.atmel.com/projects/color-clock-using-two-rgb-leds
2022-03-17 Import from https://community.atmel.com/projects/digital-clock-without-rtc
2022-03-17 Import from https://community.atmel.com/projects/ping-ultrasonic-distance-sens
2022-03-17 Import from https://community.atmel.com/projects/pctfs-memory-file-system
2022-03-17 Import from https://community.atmel.com/projects/software-uart-fifo
2022-03-17 Import from https://community.atmel.com/projects/fast-itoa-v10
2022-03-17 Import from https://community.atmel.com/projects/bascomavr-drivers-db101
2022-03-17 Import from https://community.atmel.com/projects/advanced-atx-power-supply-test
